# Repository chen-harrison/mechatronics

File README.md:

# Advanced Mechatronics

This repository contains all of my course material for the Advanced Mechatronics course (MECH_ENG 433-0) at Northwestern University.

## Topics Covered
- PIC32
- Autodesk EAGLE PCB layout
- SPI/I2C communication
- IMU
- LCD

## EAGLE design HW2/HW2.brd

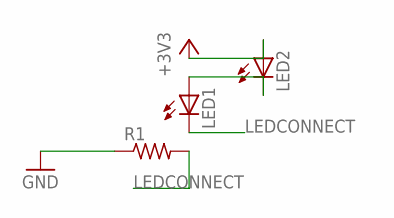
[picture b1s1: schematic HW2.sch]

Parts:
LED1, LED2: LED3MM
R1: R-US_0207/10; 0207/10

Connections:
+3V3: LED2.A
GND: R1.1
LEDCONNECT: LED1.K (C), R1.2
unnamed: LED1.A, LED2.K (C)

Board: 2 copper layers, 3 parts (0 on the bottom side), 2 nets, no tracks yet.

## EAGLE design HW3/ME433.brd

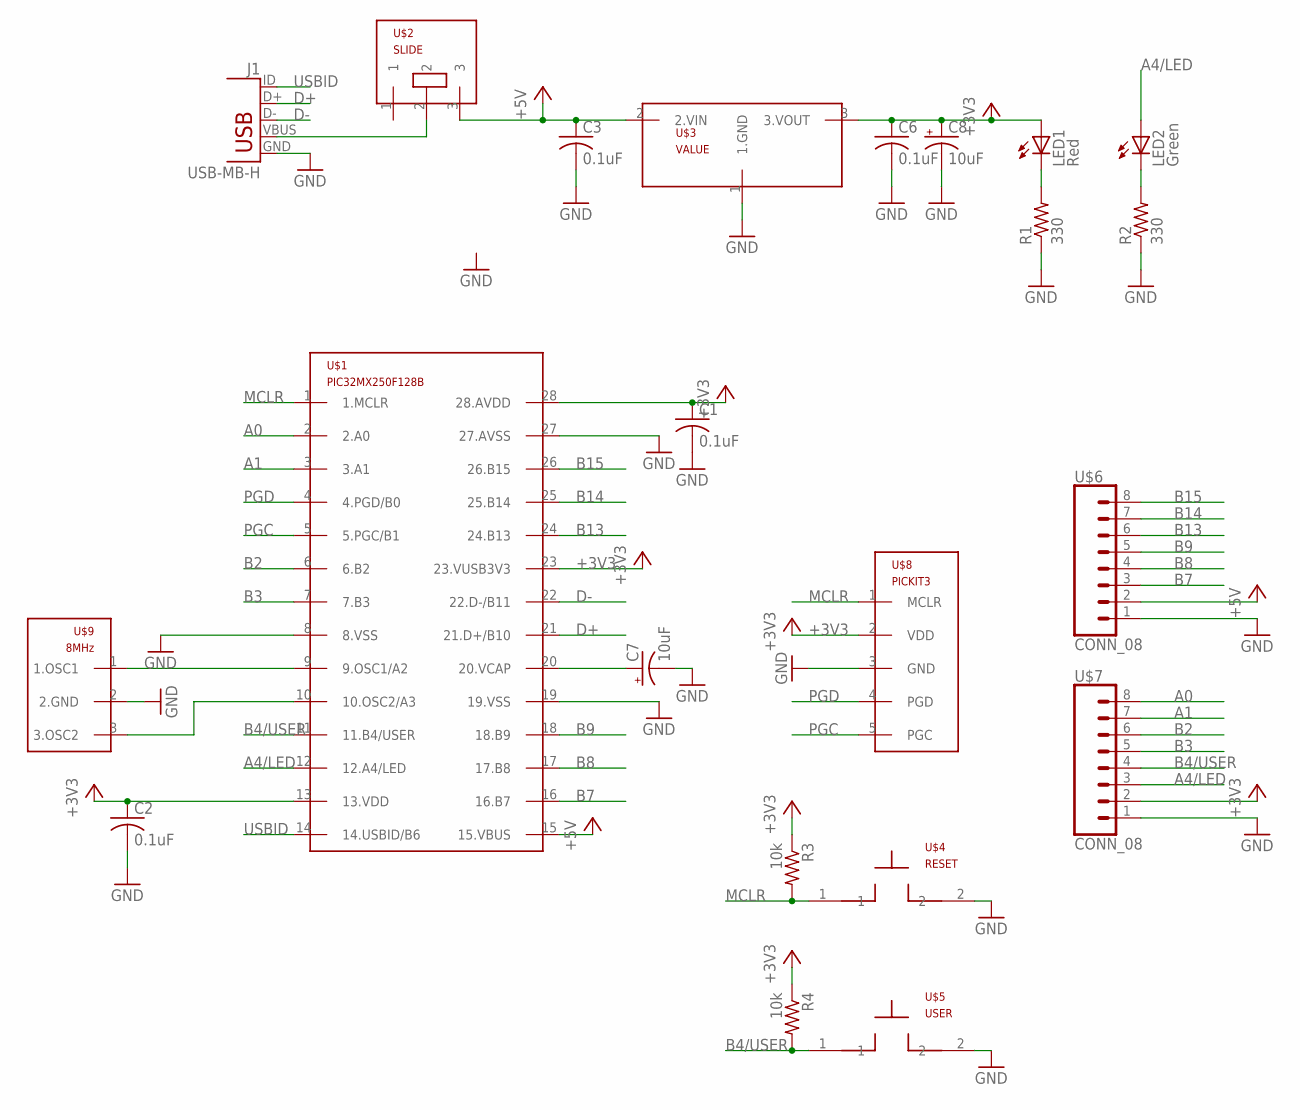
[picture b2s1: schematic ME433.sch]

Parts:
C1, C2, C3, C6: 0.1uF; C025-025X050
C7, C8: 10uF; B45181B
J1: USB-MB-H
LED1: Red; LED3MM
LED2: Green; LED3MM
R1, R2: 330; 0207/10
R3, R4: 10k; 0207/10
U$1: PIC32MX250F128B; DIL28-3
U$2: SLIDE
U$3: MCP1702; TO92
U$4: RESET; PB
U$5: USER; PB
U$6, U$7: CONN_08; 1X08
U$8: PICKIT3; 1X05
U$9: 8MHz; OSC

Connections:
+3V3: C1.1, C2.1, C6.1, C8.+, LED1.A, R3.1, R4.1, U$1.13 (13.VDD), U$1.23 (23.VUSB3V3), U$1.28 (28.AVDD), U$3.3 (3.VOUT), U$7.2, U$8.2 (VDD)
+5V: C3.1, U$1.15 (15.VBUS), U$2.3, U$3.2 (2.VIN), U$6.2
A0: U$1.2 (2.A0), U$7.8
A1: U$1.3 (3.A1), U$7.7
A4/LED: LED2.A, U$1.12 (12.A4/LED), U$7.3
B2: U$1.6 (6.B2), U$7.6
B3: U$1.7 (7.B3), U$7.5
B4/USER: R4.2, U$1.11 (11.B4/USER), U$5.1, U$7.4
B7: U$1.16 (16.B7), U$6.3
B8: U$1.17 (17.B8), U$6.4
B9: U$1.18 (18.B9), U$6.5
B13: U$1.24 (24.B13), U$6.6
B14: U$1.25 (25.B14), U$6.7
B15: U$1.26 (26.B15), U$6.8
D+: J1.D+, U$1.21 (21.D+/B10)
D-: J1.D-, U$1.22 (22.D-/B11)
GND: C1.2, C2.2, C3.2, C6.2, C7.-, C8.-, J1.GND, R1.1, R2.1, U$1.8 (8.VSS), U$1.19 (19.VSS), U$1.27 (27.AVSS), U$3.1 (1.GND), U$4.2, U$5.2, U$6.1, U$7.1, U$8.3 (GND), U$9.2 (2.GND)
MCLR: R3.2, U$1.1 (1.MCLR), U$4.1, U$8.1 (MCLR)
unnamed: J1.VBUS, U$2.2
unnamed: U$1.9 (9.OSC1/A2), U$9.1 (1.OSC1)
unnamed: U$1.10 (10.OSC2/A3), U$9.3 (3.OSC2)
unnamed: LED1.K (C), R1.2
unnamed: C7.+, U$1.20 (20.VCAP)
unnamed: LED2.K (C), R2.2
PGC: U$1.5 (5.PGC/B1), U$8.5 (PGC)
PGD: U$1.4 (4.PGD/B0), U$8.4 (PGD)
USBID: J1.ID (D+1), U$1.14 (14.USBID/B6)

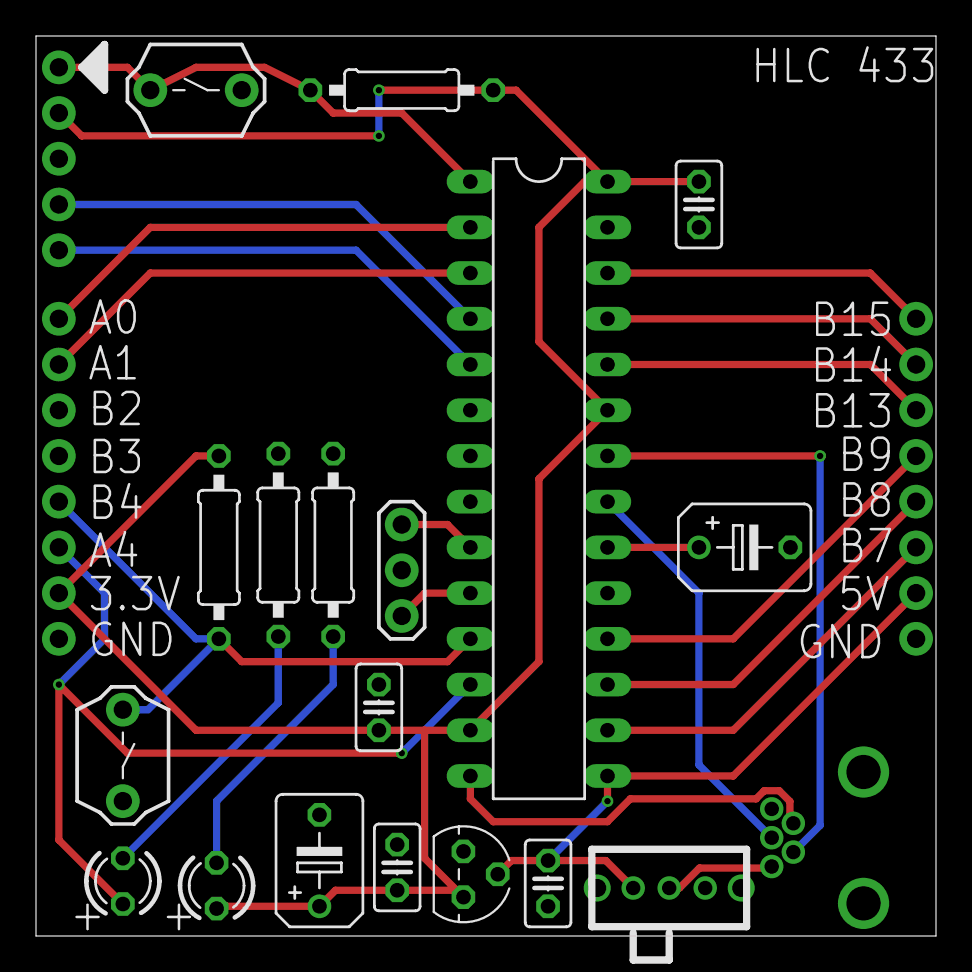
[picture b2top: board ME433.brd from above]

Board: 2 copper layers, 50.0 x 50.0 mm, 22 parts (0 on the bottom side), 27 nets.

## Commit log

2018-04-09 My first commit!
2018-04-09 Enjoy!
2018-04-10 hw1 start
2018-04-10 changed #pragma commands
2018-04-10 add LED commands
2018-04-10 add photos
2018-04-10 write while loop
2018-04-10 circuit diagram
2018-04-12 create library
2018-04-13 completed schematic
2018-04-15 finalized 1kHz frequency
2018-04-16 cleaned up HW2
2018-04-16 finished board labels
2018-04-16 added gerber files (no image)
2018-04-24 set spi1 registers
2018-04-27 functions + main
2018-05-01 generated output
2018-05-01 create framework
2018-05-07 version 1
2018-05-07 created array for output values
2018-05-11 final version
2018-05-12 actual final version
2018-05-12 final final version
2018-05-15 misc
2018-05-15 print letter
2018-06-04 initiate hw7
2018-06-04 initiate hw12
2018-06-05 initialize hw13
2018-06-13 misc stuff
2018-06-13 initial box design
2018-06-13 initial wheel design
2018-06-13 create IMU initialization function
2018-06-13 all but OLED code
2018-06-13 prints accelerometer values, but #s make no sense
2018-06-13 hw7 final
2018-06-15 hw1 duplication
2018-06-15 hw 8 redo
2018-06-15 hw8 final version
2018-06-16 hw9 start
2018-06-16 5Hz increment works
2018-06-17 hw9 final
2018-06-17 hw14 revised cdc code
2018-06-17 hw14 final submission
2018-06-17 added wheel photo
2018-06-17 hw17
2020-06-04 Makefile files not detectable by linguist
